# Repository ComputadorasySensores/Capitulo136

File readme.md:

# Pico Carrier Relay

Un placa de desarrollo para Raspberry Pi Pico/W con 3 canales de relé (relay) incorporados controlado mediante GPIOs y borneras para una fácil conexión a circuitos externos de continua y alterna.
También expone todos los GPIO de la placa para una fácil conexión de dispositivos adicionales y un pulsador de reset.

Todos los archivos de diseño en Kicad se encuentran publicados junto a un código de ejemplo en MicroPython

# Fabricación

Dentro de la carpeta `fab` encontrarás el archivo `Pico-Carrier-Relay-Fab.zip` que incluye los Gerber y archivos de perforación .drl todo listo para ordenar a tu fabricante de PCB favorito.
Para solicitar el servicio de ensamble (PCBA) en dicha carpeta `fab` encontrarás el archivo `Pico-Carrier-Relay-BOM.csv` con el listado de materiales (BOM) y el archivo `Pico-Carrier-Relay-PnP.zip` para las coordenadas
de ubicación de componentes PnP (Pick and Place).

# Paso a paso

La explicación completa la podrás ver en el siguiente video de Youtube:
https://youtu.be/5ypWmVE0PGM

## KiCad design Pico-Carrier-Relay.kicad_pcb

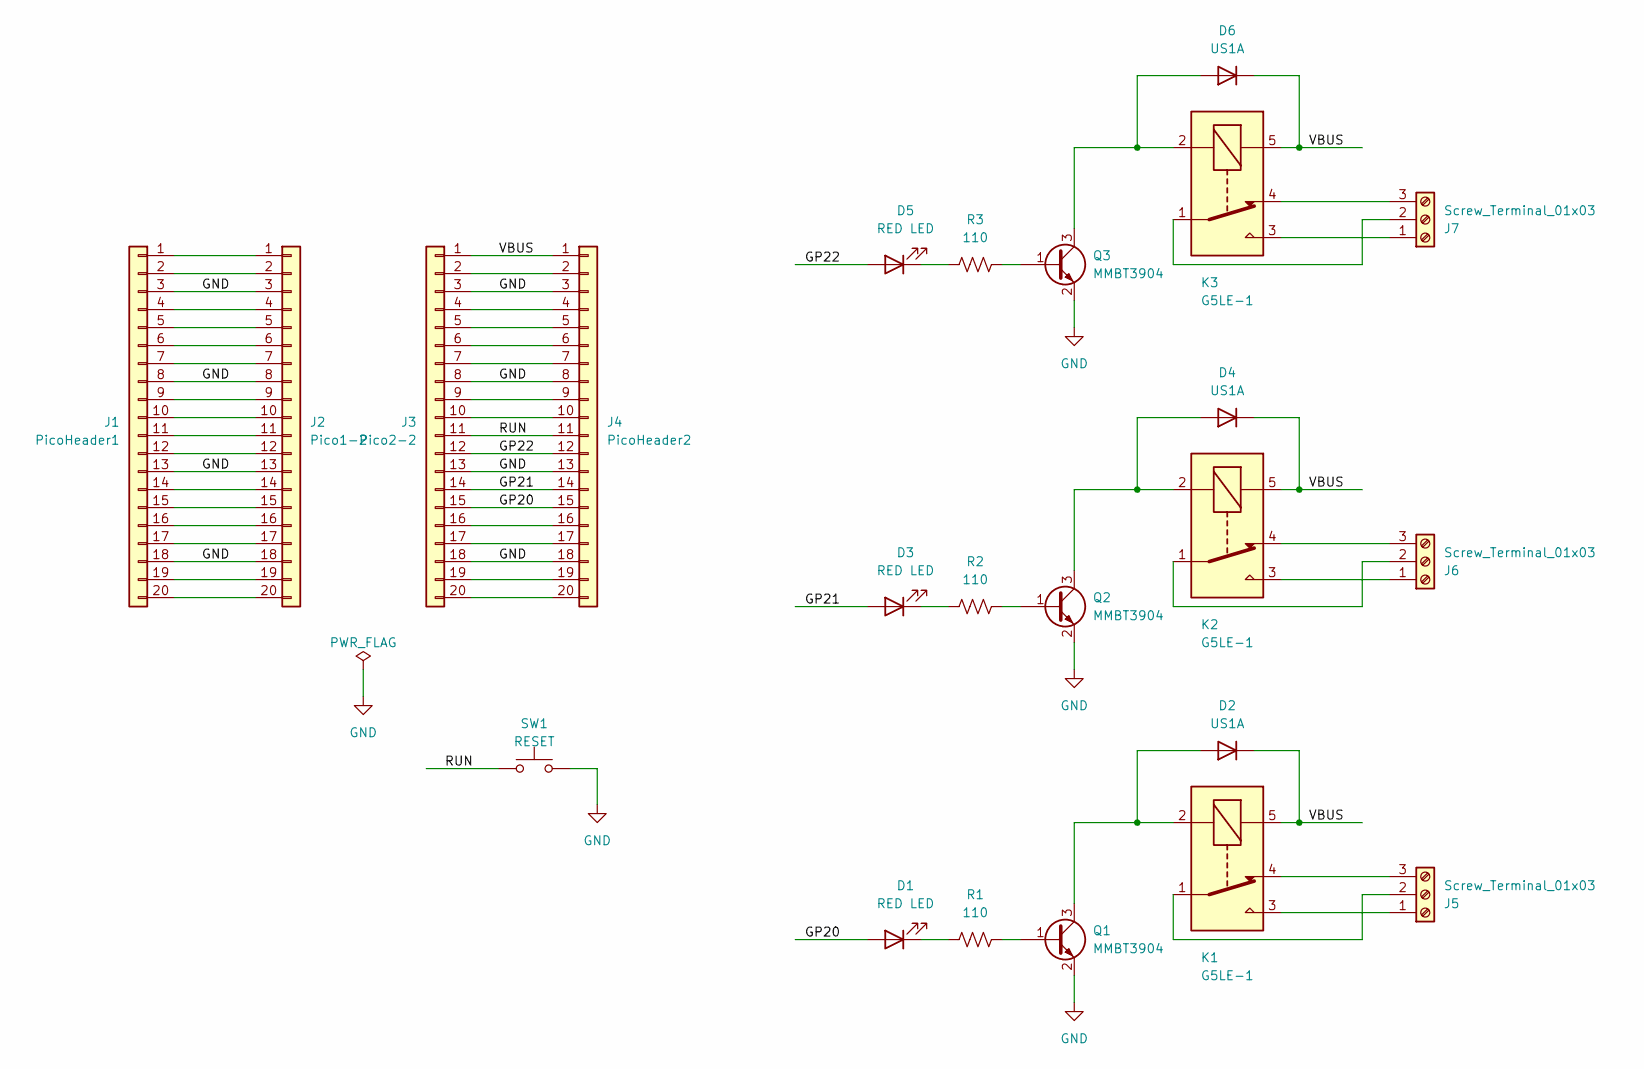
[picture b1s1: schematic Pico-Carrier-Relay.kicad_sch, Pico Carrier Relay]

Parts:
D1, D3, D5: RED LED; LED_1206_3216Metric
D2, D4, D6: US1A; D_SMA
J1: PicoHeader1; PinHeader_1x20_P2.54mm_Vertical
J2: Pico1-2; PinSocket_1x20_P2.54mm_Vertical
J3: Pico2-2; PinSocket_1x20_P2.54mm_Vertical
J4: PicoHeader2; PinHeader_1x20_P2.54mm_Vertical
J5, J6, J7: Screw_Terminal_01x03; TerminalBlock_Phoenix_MKDS-1,5-3_1x03_P5.00mm_Horizontal
K1, K2, K3: G5LE-1; Relay_SPDT_Omron-G5LE-1
Q1, Q2, Q3: MMBT3904; SOT-23
R1, R2, R3: 110; R_1206_3216Metric
SW1: RESET; SW_PUSH_6mm

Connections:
/GP20: D1.2 (A), J3.15, J4.15
/GP21: D3.2 (A), J3.14, J4.14
/GP22: D5.2 (A), J3.12, J4.12
/RUN: J3.11, J4.11, SW1.1
/VBUS: D2.1 (K), D4.1 (K), D6.1 (K), J3.1, J4.1, K1.5, K2.5, K3.5
GND: J1.3, J1.8, J1.13, J1.18, J2.3, J2.8, J2.13, J2.18, J3.3, J3.8, J3.13, J3.18, J4.3, J4.8, J4.13, J4.18, Q1.2 (E), Q2.2 (E), Q3.2 (E), SW1.2
unnamed: D1.1 (K), R1.1
unnamed: D2.2 (A), K1.2, Q1.3 (C)
unnamed: D3.1 (K), R2.1
unnamed: D4.2 (A), K2.2, Q2.3 (C)
unnamed: D5.1 (K), R3.1
unnamed: D6.2 (A), K3.2, Q3.3 (C)
unnamed: J1.1, J2.1
unnamed: J1.2, J2.2
unnamed: J1.4, J2.4
unnamed: J1.5, J2.5
unnamed: J1.6, J2.6
unnamed: J1.7, J2.7
unnamed: J1.9, J2.9
unnamed: J1.10, J2.10
unnamed: J1.11, J2.11
unnamed: J1.12, J2.12
unnamed: J1.14, J2.14
unnamed: J1.15, J2.15
unnamed: J1.16, J2.16
unnamed: J1.17, J2.17
unnamed: J1.19, J2.19
unnamed: J1.20, J2.20
unnamed: J3.2, J4.2
unnamed: J3.4, J4.4
unnamed: J3.5, J4.5
unnamed: J3.6, J4.6
unnamed: J3.7, J4.7
unnamed: J3.9, J4.9
unnamed: J3.10, J4.10
unnamed: J3.16, J4.16
unnamed: J3.17, J4.17
unnamed: J3.19, J4.19
unnamed: J3.20, J4.20
unnamed: J5.1, K1.3
unnamed: J5.2, K1.1
unnamed: J5.3, K1.4
unnamed: J6.1, K2.3
unnamed: J6.2, K2.1
unnamed: J6.3, K2.4
unnamed: J7.1, K3.3
unnamed: J7.2, K3.1
unnamed: J7.3, K3.4
unnamed: Q1.1 (B), R1.2
unnamed: Q2.1 (B), R2.2
unnamed: Q3.1 (B), R3.2

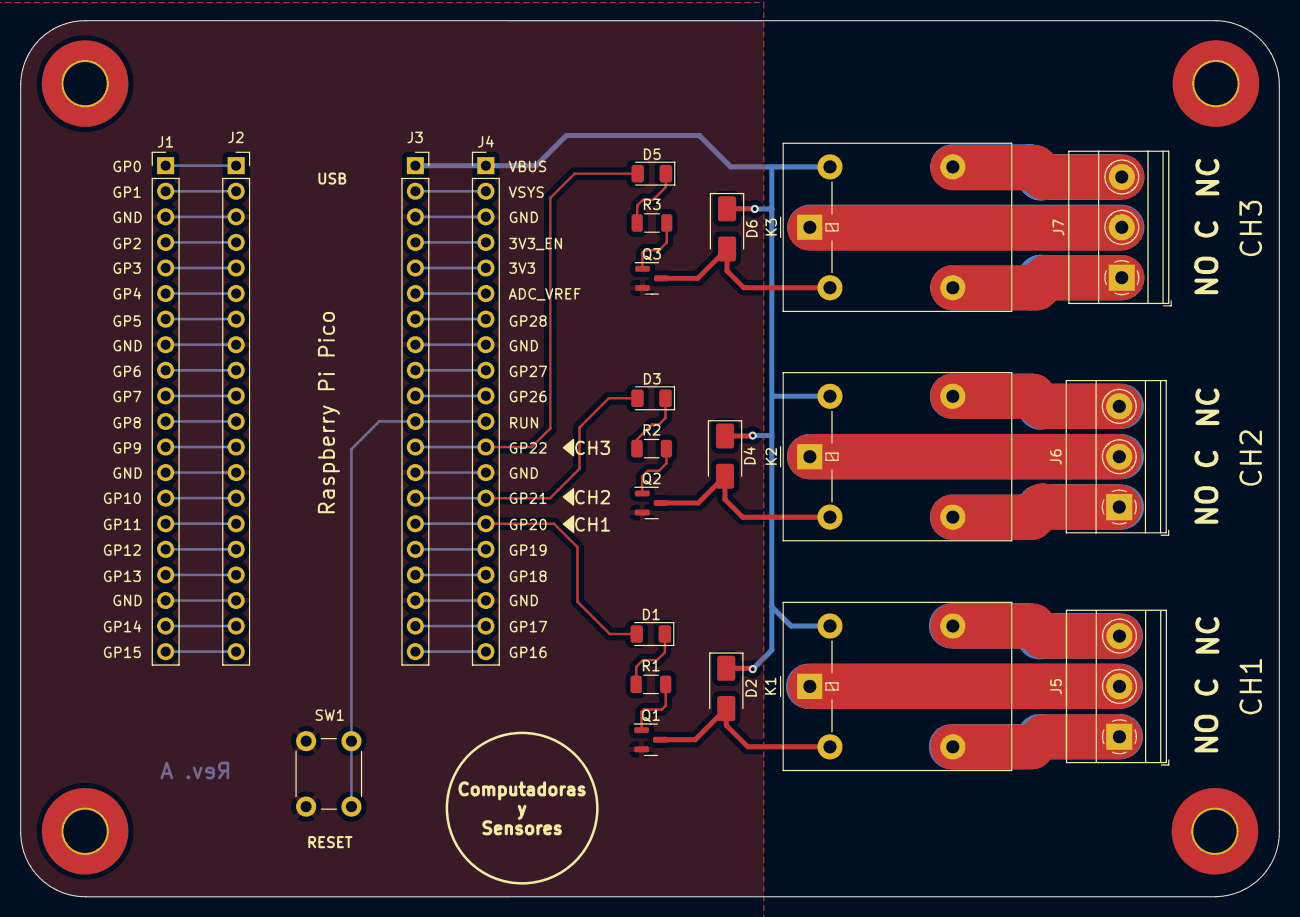
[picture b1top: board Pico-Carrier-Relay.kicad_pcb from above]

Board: 2 copper layers, 125.0 x 87.0 mm, 23 parts (0 on the bottom side), 51 nets.

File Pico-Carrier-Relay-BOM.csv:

Item #,Designator,Qty,Manufacturer,Mfg Part #,Description/Value,Package/Footprint,Type
1,"J1,J4",2,Molex,22-28-4200,Through hole pin header THT 1x20 2.54mm single row,,thru-hole
2,"D3,D5,D1",3,Dialight,598-8210-102F,LED RED CLEAR 1206,1206,smd
3,"D4,D6,D2",3,Onsemi,NRVA4007T3G,Diode 1000 V 1A Surface Mount SMA,SMA,smd
4,"J6,J5,J7",3,Phoenix contact,1715035,"TerminalBlock Phoenix MKDS-1,5-3 1x03 P5.00mm",,thru-hole
5,"R3,R1,R2",3,Panasonic,ERJ-8GEYJ111V,"±5% 0.25W, 1/4W Chip Resistor 1206 (3216 Metric) 110R",1206,smd
6,"K3,K1,K2",3,Songle Relay,SRD-05VDC-SL-C,"5V 10A SPDT (1 Form C) 5 Plugin,15.6x19.2mm Power Relay",,thru-hole
7,"J2,J3",2,Molex,90147-1120,Through hole pin socket THT 1x20 2.54mm single row,,thru-hole
8,"Q1,Q2,Q3",3,Onsemi,MMBT3904,Bipolar Transistor - BJT SOT-23 NPN,SOT-23-3,smd
9,SW1,1,Omron,B3F-1000,Tactile Switch 6X6 Flat 4.3mm Btn Force 100g,,thru-hole

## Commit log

2023-12-17 Pico-Carrier-Relay-BOM.csv
2023-12-17 servidor_web.py
2023-12-17 upload error
